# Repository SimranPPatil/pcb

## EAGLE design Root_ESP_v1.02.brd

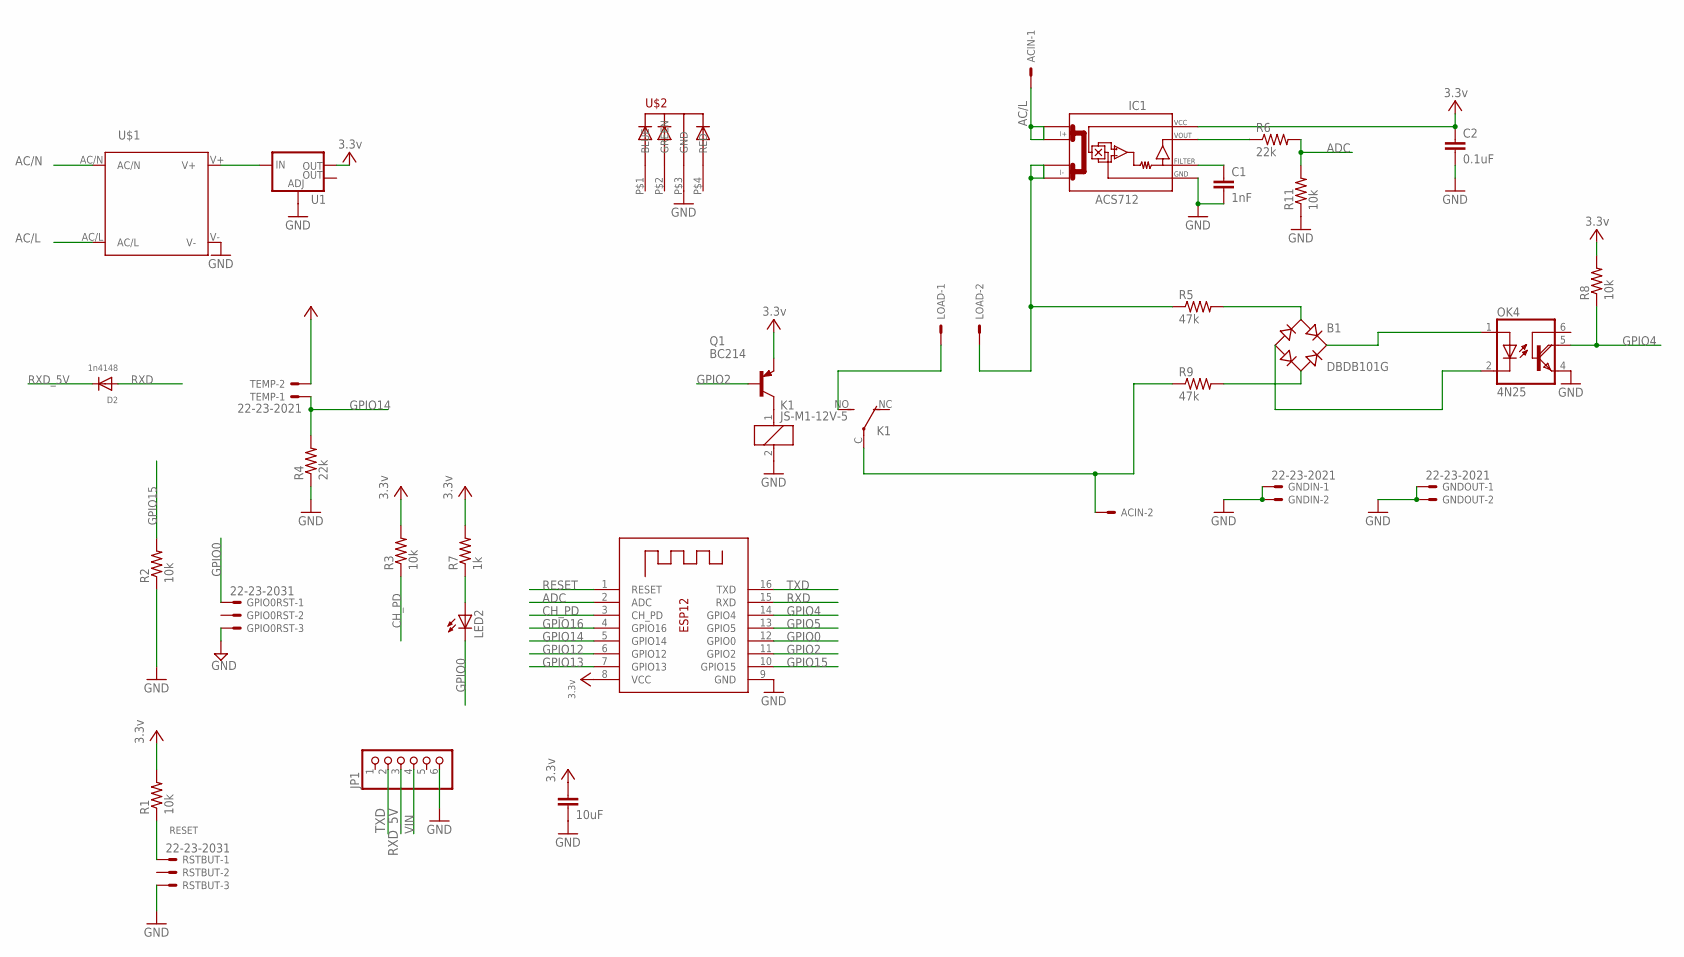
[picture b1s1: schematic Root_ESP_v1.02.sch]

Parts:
ACIN: 22-23-2021
B1: DBDB101G; DB
C1: 1nF; C5B2.5
C2: 0.1uF; C5B2.5
C3: 10uF; C5B3
D2: 1n4148; DO-1N4148
GNDIN: 22-23-2021
GNDOUT: 22-23-2021
GPIO0RST: 22-23-2031
IC1: ACS712; SO08
JP1: PINHD-1X6-3.5MM; 1X06-3.5MM
K1: JS-M1-12V-5; JS-M
LED2: LED5MM
LOAD: 22-23-2021
OK4: 4N25; DIL06
Q1: BC214; TO92
R1, R2, R3, R8, R11: 10k; 0204/7
R4, R6: 22k; 0204/7
R5, R9: 47k; 0204/7
R7: 1k; 0204/7
RSTBUT: 22-23-2031
TEMP: 22-23-2021
U1: V_REG_LM1117SOT223; SOT223
U$1: IRM_03IRM_03; IRM_03
U$2: 5MMRGBLED; LED5MMRGB
X1: ESP-12

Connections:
3.3V: R1.2
AC/L: ACIN.1, IC1.1 (I+_0), IC1.2 (I+_1), U$1.AC/L
AC/N: ACIN.2, K1.C, R9.1, U$1.AC/N
ADC: R6.2, R11.2, X1.2 (ADC)
CH_PD: R3.1, X1.3 (CH_PD)
GND: C1.2, C2.2, C3.2, GNDIN.1, GNDIN.2, GNDOUT.1, GNDOUT.2, GPIO0RST.3, IC1.5 (GND), JP1.6, K1.2, OK4.4 (E), R2.1, R4.1, R11.1, RSTBUT.3, U1.1 (ADJ), U$1.V-, U$2.P$3 (GND), X1.9 (GND)
GPIO0: GPIO0RST.1, LED2.K (C), X1.12 (GPIO0)
GPIO2: Q1.2 (B), X1.11 (GPIO2)
GPIO4: OK4.5 (COL), R8.1, X1.14 (GPIO4)
GPIO5: X1.13 (GPIO5)
GPIO12: X1.6 (GPIO12)
GPIO13: X1.7 (GPIO13)
GPIO14: R4.2, TEMP.1, X1.5 (GPIO14)
GPIO15: R2.2, X1.10 (GPIO15)
GPIO16: X1.4 (GPIO16)
LOAD/L: IC1.3 (I-_0), IC1.4 (I-_1), LOAD.2, R5.1
LOAD/N: K1.NO (S), LOAD.1
unnamed: B1.AC1, R5.2
unnamed: C1.1, IC1.6 (FILTER)
unnamed: B1.AC2, R9.2
unnamed: B1.+, OK4.1 (A)
unnamed: B1.-, OK4.2 (C)
unnamed: LED2.A, R7.1
unnamed: IC1.7 (VOUT), R6.1
unnamed: K1.1, Q1.3 (C)
unnamed: U1.3 (IN), U$1.V+
RESET: R1.1, RSTBUT.1, X1.1 (RESET)
RXD: D2.A, X1.15 (RXD)
RXD_5V: D2.C, JP1.3
TXD: JP1.2, X1.16 (TXD)
VCC: C2.1, C3.1, IC1.8 (VCC), Q1.1 (E), R3.2, R7.2, R8.2, TEMP.2, U1.2 (OUT), X1.8 (VCC)
VIN: JP1.4

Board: 2 copper layers, 32 parts (0 on the bottom side), 26 nets, no tracks yet.

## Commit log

2016-07-18 PCB compact first commit
2016-07-21 New has the latest pcbs designs

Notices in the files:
parts and their libraries:
SparkFun-PowerIC: Licensing: Creative Commons ShareAlike 4.0 International - https://creativecommons.org/licenses/by-sa/4.0
